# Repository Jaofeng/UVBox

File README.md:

# 自製 UV 紫外線曝光控制器
本控制器以 Arduino 的 ATMEGA328P 為核心，控制 UV LED 燈板，作為 DIY PCB 曝光用。

## 目錄
* [控制器硬體概要說明](#控制器硬體概要說明)
* [Arduino 程式功能](#arduino-程式功能)
* [原理圖與板線圖](#原理圖與板線圖)
* [實做範例](#實做範例)

## 控制器硬體概要說明
控制器分為兩版本：595 版與 I2C LCD 版。  
兩版本電路、功能都大同小異，最大差別在於 595 版是使用 74x595 控制七段顯示器作為顯示；I2C LCD 則是使用 PCF8574 控制 1602 的 LCD(相容HD44780)。  
I2C LCD 版提供 USB 界面(使用 FT232R)，可直接修改 Arduino 程式；而 595 版本就必須使用 ICSP 界面進行更新。

使用 4 + 1 個按鍵共 5 個按鍵進行控制：
* Start : 開始曝光
* Mode : 選擇模式  
    * 同時點亮上下兩板  
    * 僅點亮上板  
    * 僅點亮下板  
    * 亮度調整模式  
* Up / Dn :  
    * 亮度調整模式：增加/減少亮度值，增減量 +/- 5%
    * 其餘模式：增加/減少秒數，增減量 10 秒
* Reset : 重新啟動

595 版是第一個版本，小弟先用麵包版電路作第一片 595 版的 PCB，再用他去做其他的 PCB。

使用一般 Notebook 電源供應器(DC 19V)做為電源輸入，由於電路主要電壓使用 5V，為避免壓差太大，造成降壓晶片過熱燒毀，所以我做了兩次降壓：19v -> 12v -> 5v。  
由 ULN2003 控制 UV LED 燈板，也就是燈板部分直接使用 19V 電源。

在此不提供 UV LED 燈板的電路，我使用 5 串 1 並 14 的方式組成一片燈板，意思就是 5 顆 UV LED 與 1 顆限流電阻為一組做串聯，一共有 14 組併聯(請參閱下方照片)。    
LED 間距約為 7 x 2.54 mm。

依 LED 編排密度、曝光亮度、燈板高度、線路複雜度、感光 PCB 有效期、遮色片材質等等因素，都會互相影響，所以建議各位自行實驗，找出適合的亮度、時間與燈板高度。

以小弟的經驗是：
* 線路片使用噴墨投影片，兩張重疊，增加黑色遮光效果
* 燈板高度約 7cm
* 亮度 70%
* 時間 90s~110s 不等

以上述條件，即可成功製作一片漂亮的 PCB 線路。

對了，很基本的一件事：遮色片與感光 PCB 一定要夾緊，不能有任何間隙，否則非常容易失敗。

還有，UV 紫外線很傷眼睛，為了您的眼睛著想，建議戴著抗 UV 的鏡片，以及也不要讓皮膚長時間曝曬紫外線的環境下喔... 

***

## Arduino 程式功能
開始曝光後，會顯示倒數時間，曝光時間結束時會將燈板關閉且蜂鳴器會發出警示音。

控制功能：
* 可單一控制上下燈板
* 亮度調整範圍自 0% ~ 100%
* 時間可調整範圍自 0s ~ 600s
* 曝光時間結束時，自動關閉光板，並響起警示音
* 警示音響起時，按任何一鍵停止響音

***
## 原理圖與板線圖
595版  

I2C LCD版  

***
## 實做範例
UV LED 燈板與控制板(595)    

595 版正反面    

自製 USB to UART 轉接板

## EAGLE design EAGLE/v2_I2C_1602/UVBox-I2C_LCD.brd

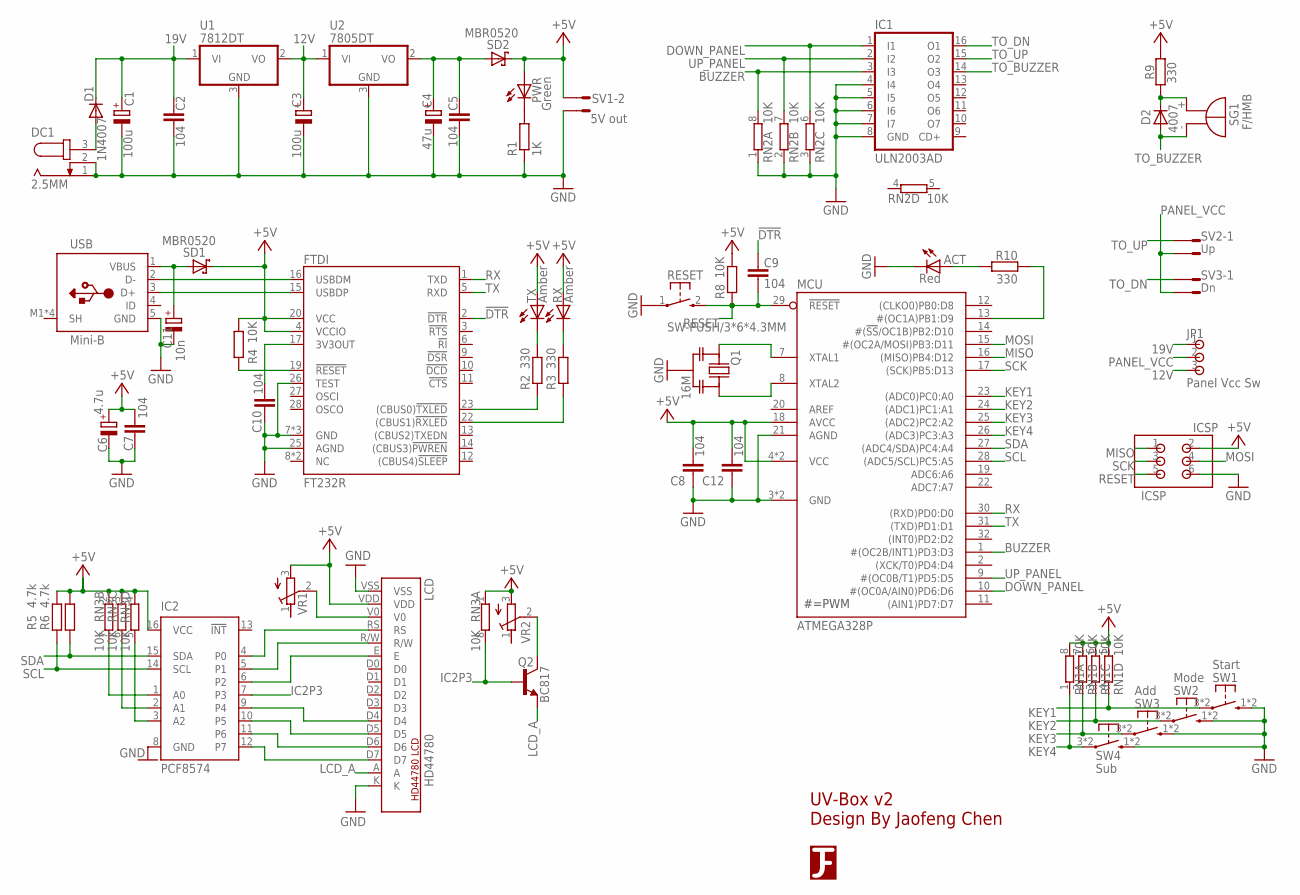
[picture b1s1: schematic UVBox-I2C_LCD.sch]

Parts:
ACT: Red; CHIPLED_0805
C1: 100u; 140CLH-0810
C2, C5: 104; C0805
C3: 100u; SMC_C
C4: 47u; SMC_C
C6: 4.7u; SMC_B
C7, C8, C9, C10, C12: 104; C0603
C11: 10n; SMC_A
D1: 1N4007; DO-214AC
D2: 4007; DO214AA
DC1: 2.5MM; SPC4078
FTDI: FT232R; SSOP28
IC1: ULN2003AD; SO16(R-PDSO-G16)
IC2: PCF8574; SO16W
ICSP: ICSP; DIP-2.54-2X3
JP1: Panel Vcc Sw; DIP-2.54-1X3
LCD: HD44780; LCD_1602
MCU: ATMEGA328P; TQFP32
PWR: Green; CHIPLED_0805
Q1: 16M; CSTCE
Q2: BC817; SOT23-BEC
R1: 1K; R0603
R2, R3, R9, R10: 330; R0603
R4, R8: 10K; R0603
R5, R6: 4.7k; R0603
RESET: SW-PUSH/3*6*4.3MM; SW-3*6*4.3MM
RN1, RN2, RN3: 10K; CAY16
RX: Amber; CHIPLED_0805
SD1, SD2: MBR0520; SOD123
SG1: F/HMB
SV1: 5V out; L02P
SV2: Up; L02P
SV3: Dn; L02P
SW1: Start; SW-6*6*3.8MM
SW2: Mode; SW-6*6*3.8MM
SW3: Add; SW-6*6*3.8MM
SW4: Sub; SW-6*6*3.8MM
TX: Amber; CHIPLED_0805
U1: 7812DT; TO252
U2: 7805DT; TO252
U$2: LOGO-3B; LOGO-3-B
USB: Mini-B; USB-MINI-B(NO_HOLE)
VR1, VR2: R-TRIMMT93XA; RTRIMT93XA

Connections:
12V: C3.+, JP1.3, U1.2 (VO), U2.1 (VI)
19V: C1.+, C2.1, D1.C, JP1.1, U1.1 (VI)
!DTR: C9.2, FTDI.2 (!DTR)
!RESET: FTDI.19 (!RESET), R4.1
!RXLED: FTDI.22 ((CBUS1)!RXLED), R3.1
!TXLED: FTDI.23 ((CBUS0)!TXLED), R2.1
+5V: C6.+, C7.1, C8.2, C12.2, FTDI.4 (VCCIO), FTDI.20 (VCC), IC2.16 (VCC), ICSP.2, LCD.VDD, MCU.4 (VCC), MCU.6 (VCC), MCU.18 (AVCC), PWR.A, R4.2, R5.1, R6.1, R8.2, R9.2, RN1.5 (2), RN1.6 (2), RN1.7 (2), RN1.8 (2), RN3.1, RN3.2 (1), RN3.3 (1), RN3.4 (1), RX.A, SD1.K, SD2.K, SV1.2, TX.A, VR1.3 (A), VR2.3 (A)
A0: IC2.1 (A0), RN3.7 (2)
A1: IC2.2 (A1), RN3.6 (2)
A2: IC2.3 (A2), RN3.5 (2)
ACT_LED: ACT.A, R10.2
BUZZER: IC1.3 (I3), MCU.1 (#(OC2B/INT1)PD3:D3), RN2.8 (2)
D+: FTDI.15 (USBDP), USB.3 (D+)
D-: FTDI.16 (USBDM), USB.2 (D-)
DOWN_PANEL: IC1.1 (I1), MCU.10 (#(OC0A/AIN0)PD6:D6), RN2.6 (2)
E: IC2.6 (P2), LCD.E
GND: ACT.C, C1.-, C2.2, C3.-, C4.-, C5.2, C6.-, C7.2, C8.1, C10.1, C11.-, C12.1, DC1.1, DC1.2, FTDI.7 (GND), FTDI.18 (GND), FTDI.21 (GND), FTDI.25 (AGND), FTDI.26 (TEST), IC1.4 (I4), IC1.5 (I5), IC1.6 (I6), IC1.7 (I7), IC1.8 (GND), IC2.8 (GND), ICSP.6, LCD.K, LCD.VSS, MCU.3 (GND), MCU.5 (GND), MCU.21 (AGND), Q1.2 (GND), R1.1, RESET.1, RN2.1, RN2.2 (1), RN2.3 (1), SV1.1, SW1.1 (S), SW1.2 (S), SW2.1 (S), SW2.2 (S), SW3.1 (S), SW3.2 (S), SW4.1 (S), SW4.2 (S), U1.3 (GND), U2.3 (GND), USB.5 (GND)
IC2P3: IC2.7 (P3), Q2.B, RN3.8 (2)
KEY1: MCU.23 ((ADC0)PC0:A0), RN1.4 (1), SW1.3, SW1.4
KEY2: MCU.24 ((ADC1)PC1:A1), RN1.3 (1), SW2.3, SW2.4
KEY3: MCU.25 ((ADC2)PC2:A2), RN1.2 (1), SW3.3, SW3.4
KEY4: MCU.26 ((ADC3)PC3:A3), RN1.1, SW4.3, SW4.4
LCD_A: LCD.A, Q2.E
MISO: ICSP.1, MCU.16 ((MISO)PB4:D12)
MOSI: ICSP.4, MCU.15 (#(OC2A/MOSI)PB3:D11)
unnamed: C11.+, SD1.A, USB.1 (VBUS)
unnamed: C4.+, C5.1, SD2.A, U2.2 (VO)
unnamed: D1.A, DC1.3
unnamed: PWR.C, R1.2
unnamed: Q2.C, VR2.2 (S)
unnamed: R2.2, TX.C
unnamed: R3.2, RX.C
unnamed: D2.C, R9.1, SG1.+
unnamed: IC2.12 (P7), LCD.D7
unnamed: IC2.11 (P6), LCD.D6
unnamed: IC2.10 (P5), LCD.D5
unnamed: IC2.9 (P4), LCD.D4
unnamed: C10.2, FTDI.17 (3V3OUT)
PANEL_VCC: JP1.2, SV2.2, SV3.2
PB1: MCU.13 (#(OC1A)PB1:D9), R10.1
R/W: IC2.5 (P1), LCD.R/W
RESET: C9.1, ICSP.5, MCU.29 (!RESET), R8.1, RESET.2 (S)
RS: IC2.4 (P0), LCD.RS
RX: FTDI.1 (TXD), MCU.30 ((RXD)PD0:D0)
SCK: ICSP.3, MCU.17 ((SCK)PB5:D13)
SCL: IC2.14 (SCL), MCU.28 ((ADC5/SCL)PC5:A5), R5.2
SDA: IC2.15 (SDA), MCU.27 ((ADC4/SDA)PC4:A4), R6.2
TO_BUZZER: D2.A, IC1.14 (O3), SG1.-
TO_DN: IC1.16 (O1), SV3.1
TO_UP: IC1.15 (O2), SV2.1
TX: FTDI.5 (RXD), MCU.31 ((TXD)PD1:D1)
UP_PANEL: IC1.2 (I2), MCU.9 (#(OC0B/T1)PD5:D5), RN2.7 (2)
VD: LCD.V0, VR1.2 (S)
XTAL1: MCU.7 (XTAL1), Q1.1 (IN)
XTAL2: MCU.8 (XTAL2), Q1.3 (OUT)

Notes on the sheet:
UV-Box v2 Design By Jaofeng Chen

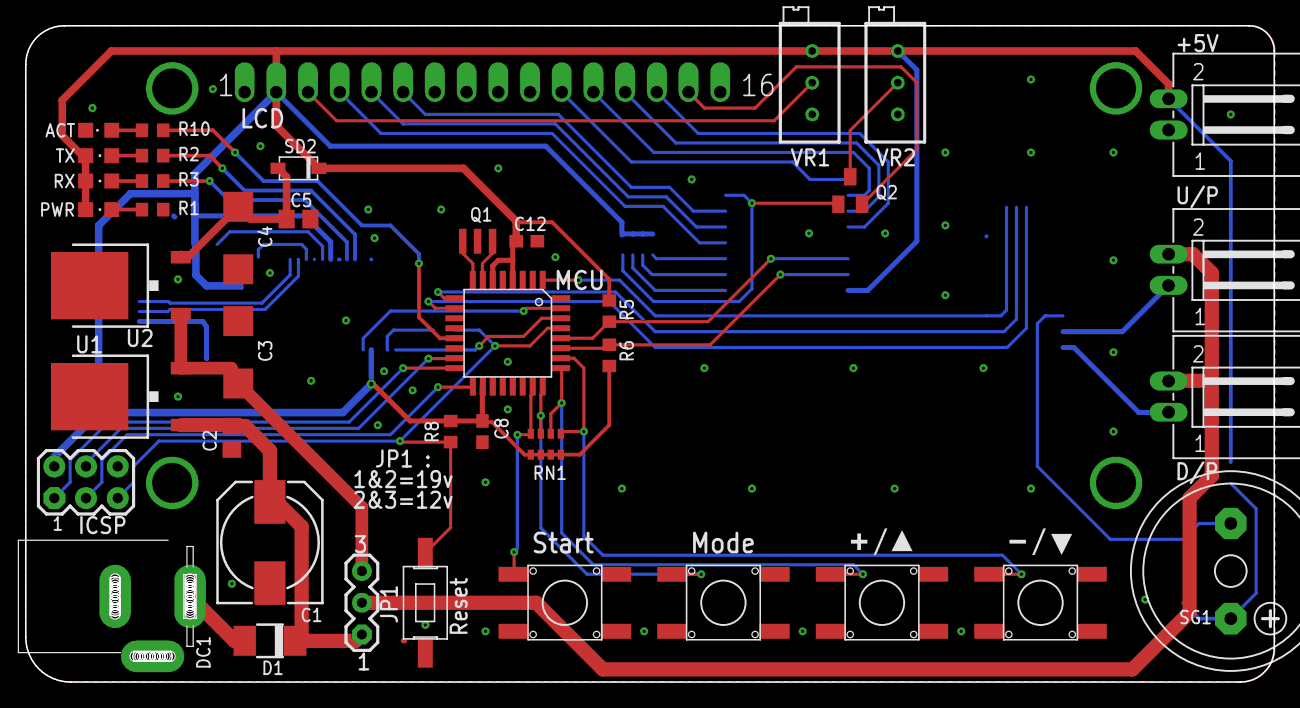
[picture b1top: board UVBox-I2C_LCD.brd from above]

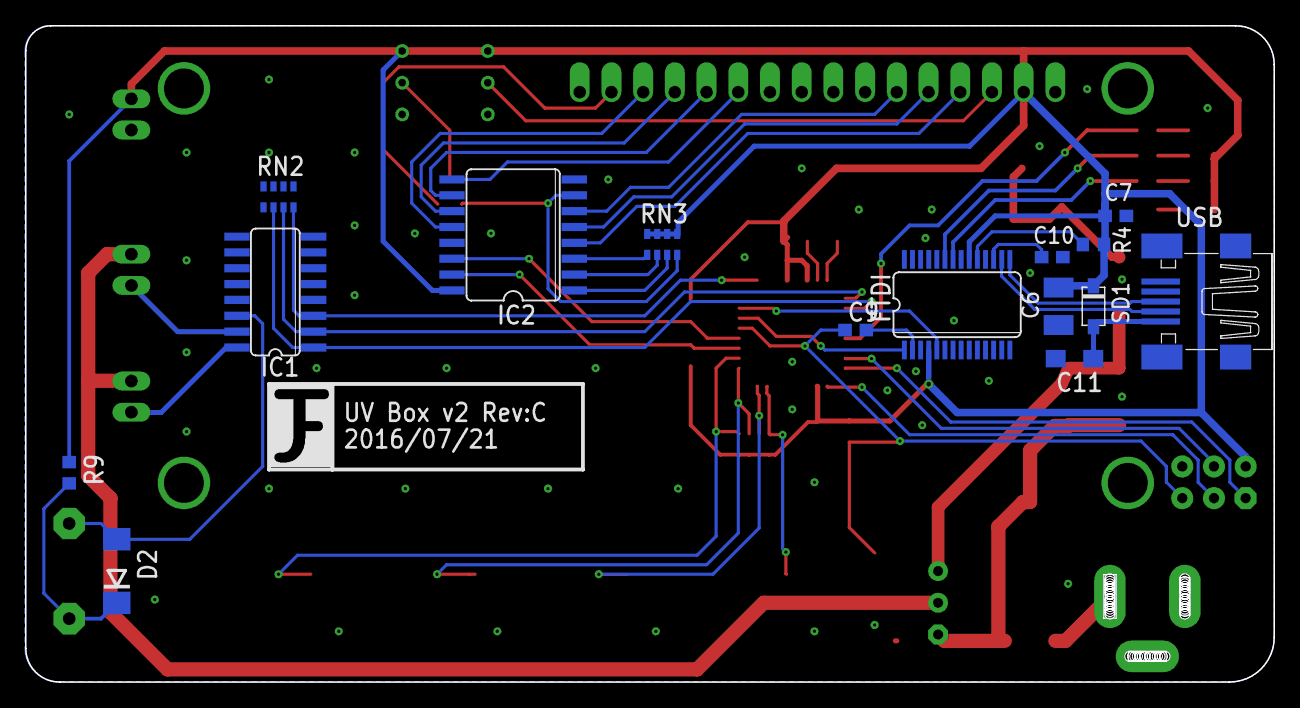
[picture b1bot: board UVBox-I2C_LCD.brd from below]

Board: 2 copper layers, 100.0 x 52.6 mm, 59 parts (15 on the bottom side), 55 nets.

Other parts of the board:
U$1: TEXT_UP
U$3: TEXT_DN

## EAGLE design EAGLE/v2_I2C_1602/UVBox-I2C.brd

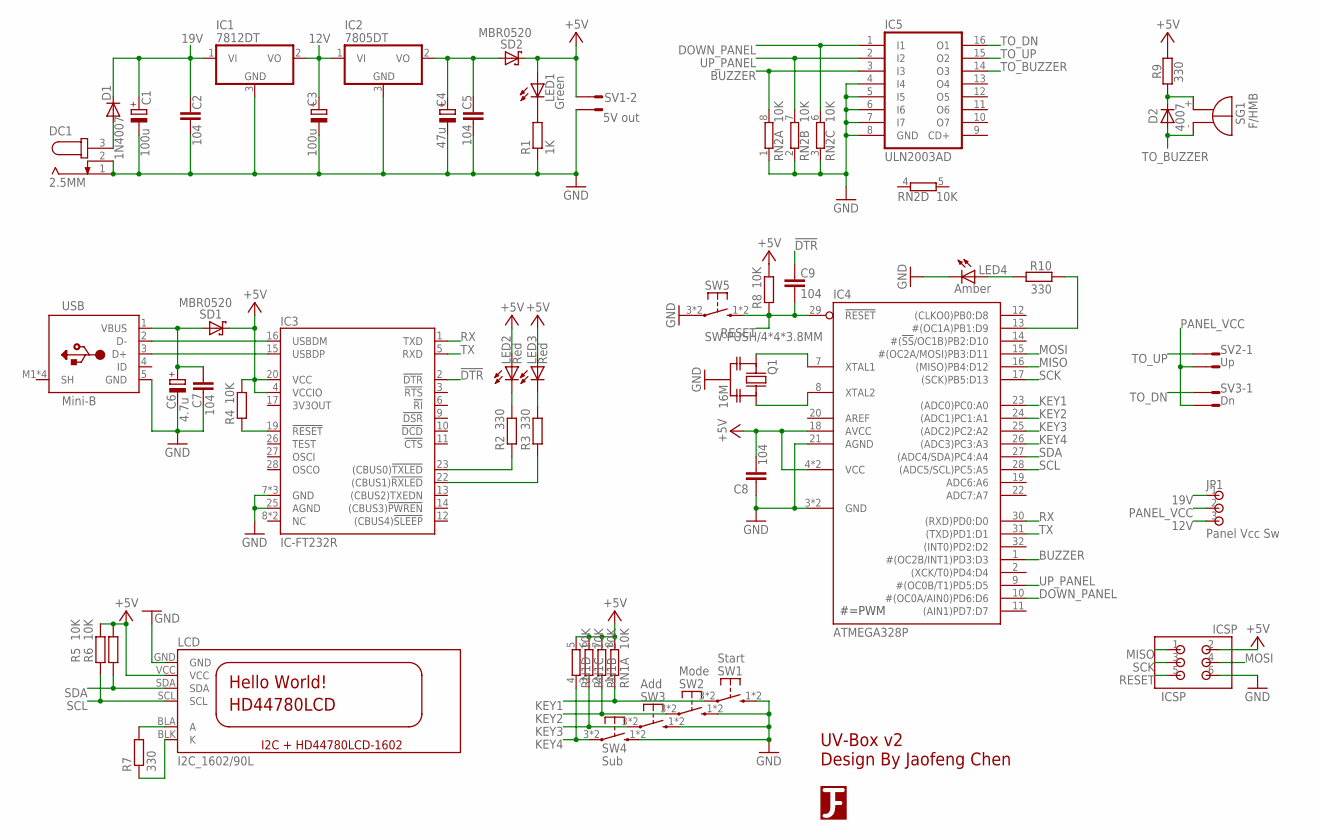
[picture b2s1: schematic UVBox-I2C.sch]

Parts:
C1: 100u; 140CLH-0810
C2, C5, C7, C8, C9: 104; C0805
C3: 100u; SMC_C
C4: 47u; SMC_C
C6: 4.7u; SMC_C
D1: 1N4007; DO-214AC
D2: 4007; DO214AA
DC1: 2.5MM; SPC4078
IC1: 7812DT; TO252
IC2: 7805DT; TO252
IC3: IC-FT232R; SSOP28
IC4: ATMEGA328P; TQFP32
IC5: ULN2003AD; SO16
ICSP: ICSP; DIP-2.54-2X3
JP1: Panel Vcc Sw; DIP-2.0-1X3
LCD: I2C_1602/90L
LED1: Green; CHIPLED_1206
LED2, LED3: Red; CHIPLED_1206
LED4: Amber; CHIPLED_1206
Q1: 16M; CSTCE
R1: 1K; R0805
R2, R3, R7, R9, R10: 330; R0805
R4, R5, R6, R8: 10K; R0805
RN1, RN2: 10K; CAY16
SD1, SD2: MBR0520; SOD123
SG1: F/HMB
SV1: 5V out; L02P
SV2: Up; L02P
SV3: Dn; L02P
SW1: Start; SW-6*6*3.8MM
SW2: Mode; SW-6*6*3.8MM
SW3: Add; SW-6*6*3.8MM
SW4: Sub; SW-6*6*3.8MM
SW5: SW-PUSH/4*4*3.8MM; SW-4*4*3.8MM
U$2: LOGO-3
USB: Mini-B; USB-MINI-B(NO_HOLE)

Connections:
12V: C3.+, IC1.2 (VO), IC2.1 (VI), JP1.3
19V: C1.+, C2.1, D1.C, IC1.1 (VI), JP1.1
!DTR: C9.2, IC3.2 (!DTR)
+5V: C8.2, IC3.4 (VCCIO), IC3.20 (VCC), IC4.4 (VCC), IC4.6 (VCC), IC4.18 (AVCC), ICSP.2, LCD.VCC, LED1.A, LED2.A, LED3.A, R4.2, R5.1, R6.1, R8.2, R9.2, RN1.5 (2), RN1.6 (2), RN1.7 (2), RN1.8 (2), SD1.K, SD2.K, SV1.2
BUZZER: IC4.1 (#(OC2B/INT1)PD3:D3), IC5.3 (I3), RN2.8 (2)
DOWN_PANEL: IC4.10 (#(OC0A/AIN0)PD6:D6), IC5.1 (I1), RN2.6 (2)
GND: C1.-, C2.2, C3.-, C4.-, C5.2, C6.-, C7.2, C8.1, DC1.1, DC1.2, IC1.3 (GND), IC2.3 (GND), IC3.7 (GND), IC3.18 (GND), IC3.21 (GND), IC3.25 (AGND), IC4.3 (GND), IC4.5 (GND), IC4.21 (AGND), IC5.4 (I4), IC5.5 (I5), IC5.6 (I6), IC5.7 (I7), IC5.8 (GND), ICSP.6, LCD.GND, LED4.C, Q1.2 (GND), R1.1, RN2.1, RN2.2 (1), RN2.3 (1), SV1.1, SW1.1 (S), SW1.2 (S), SW2.1 (S), SW2.2 (S), SW3.1 (S), SW3.2 (S), SW4.1 (S), SW4.2 (S), SW5.3, SW5.4, USB.5 (GND)
KEY1: IC4.23 ((ADC0)PC0:A0), RN1.1, SW1.3, SW1.4
KEY2: IC4.24 ((ADC1)PC1:A1), RN1.2 (1), SW2.3, SW2.4
KEY3: IC4.25 ((ADC2)PC2:A2), RN1.3 (1), SW3.3, SW3.4
KEY4: IC4.26 ((ADC3)PC3:A3), RN1.4 (1), SW4.3, SW4.4
MISO: IC4.16 ((MISO)PB4:D12), ICSP.1
MOSI: IC4.15 (#(OC2A/MOSI)PB3:D11), ICSP.4
unnamed: C6.+, C7.1, SD1.A, USB.1 (VBUS)
unnamed: C4.+, C5.1, IC2.2 (VO), SD2.A
unnamed: D1.A, DC1.3
unnamed: IC3.19 (!RESET), R4.1
unnamed: IC4.7 (XTAL1), Q1.1 (IN)
unnamed: LED1.C, R1.2
unnamed: IC3.16 (USBDM), USB.2 (D-)
unnamed: LCD.BLK (K), R7.1
unnamed: LCD.BLA (A), R7.2
unnamed: IC3.15 (USBDP), USB.3 (D+)
unnamed: LED2.C, R2.2
unnamed: LED3.C, R3.2
unnamed: D2.C, R9.1, SG1.+
unnamed: IC3.23 ((CBUS0)!TXLED), R2.1
unnamed: IC3.22 ((CBUS1)!RXLED), R3.1
unnamed: LED4.A, R10.2
unnamed: IC4.13 (#(OC1A)PB1:D9), R10.1
unnamed: IC4.8 (XTAL2), Q1.3 (OUT)
PANEL_VCC: JP1.2, SV2.2, SV3.2
RESET: C9.1, IC4.29 (!RESET), ICSP.5, R8.1, SW5.1 (S), SW5.2 (S)
RX: IC3.1 (TXD), IC4.30 ((RXD)PD0:D0)
SCK: IC4.17 ((SCK)PB5:D13), ICSP.3
SCL: IC4.28 ((ADC5/SCL)PC5:A5), LCD.SCL, R5.2
SDA: IC4.27 ((ADC4/SDA)PC4:A4), LCD.SDA, R6.2
TO_BUZZER: D2.A, IC5.14 (O3), SG1.-
TO_DN: IC5.16 (O1), SV3.1
TO_UP: IC5.15 (O2), SV2.1
TX: IC3.5 (RXD), IC4.31 ((TXD)PD1:D1)
UP_PANEL: IC4.9 (#(OC0B/T1)PD5:D5), IC5.2 (I2), RN2.7 (2)

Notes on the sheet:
UV-Box v2 Design By Jaofeng Chen

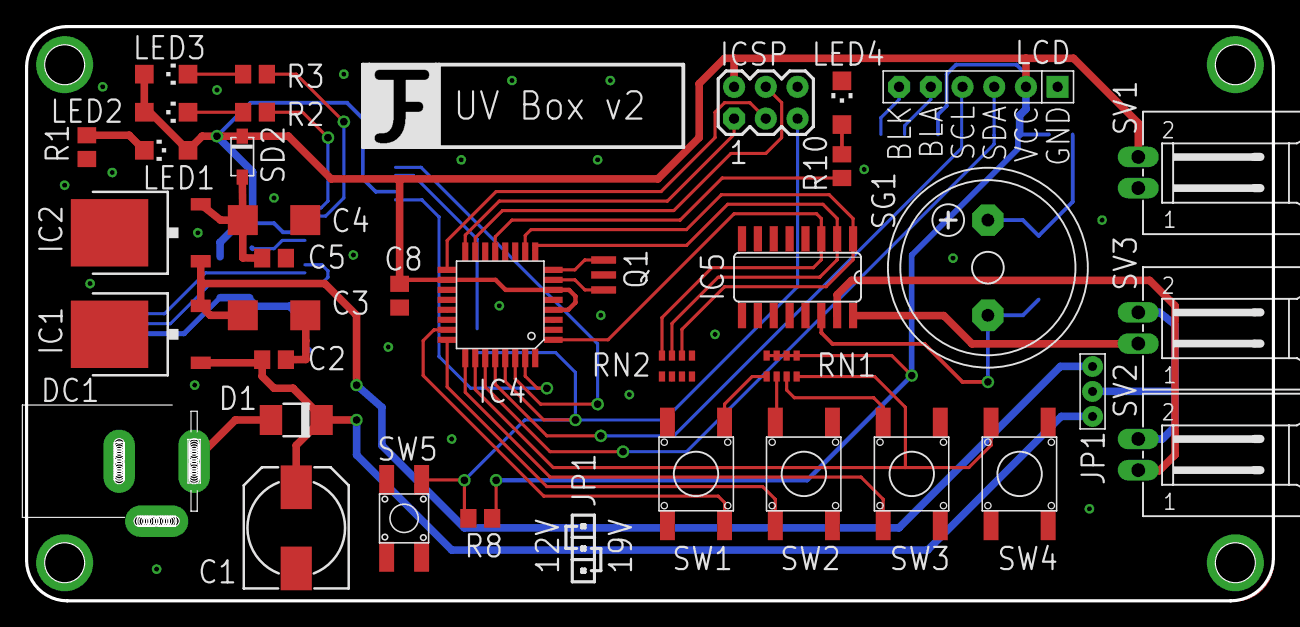
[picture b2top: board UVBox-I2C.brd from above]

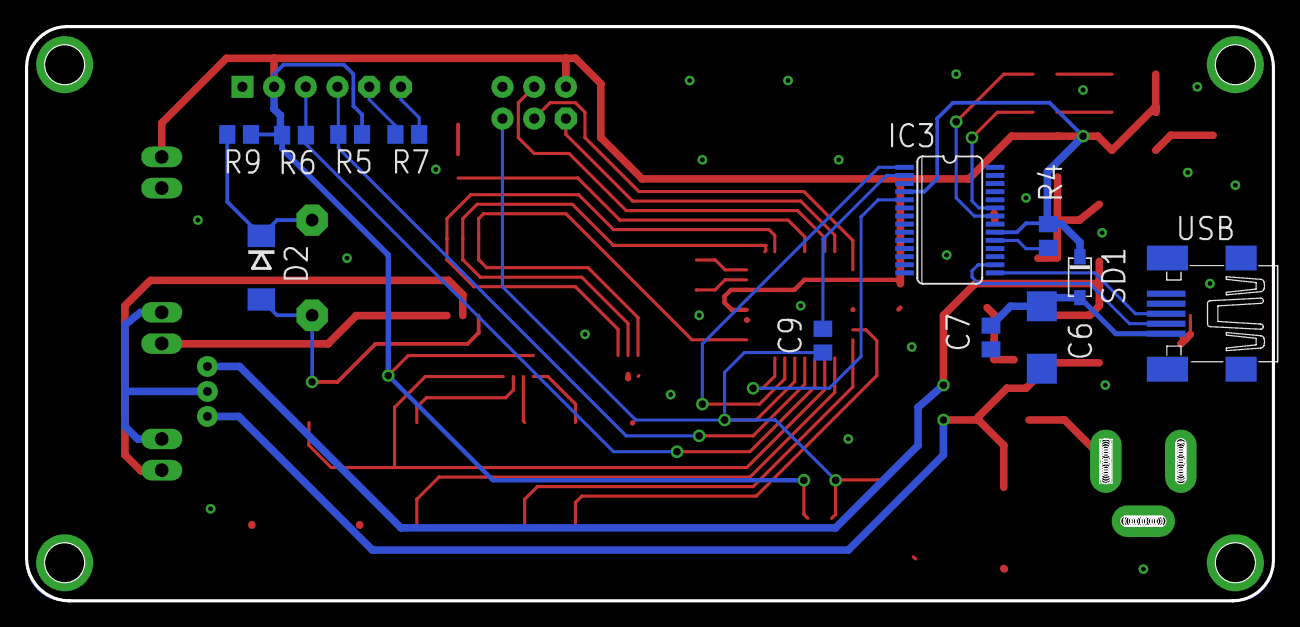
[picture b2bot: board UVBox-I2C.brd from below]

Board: 2 copper layers, 99.8 x 46.0 mm, 50 parts (12 on the bottom side), 42 nets.

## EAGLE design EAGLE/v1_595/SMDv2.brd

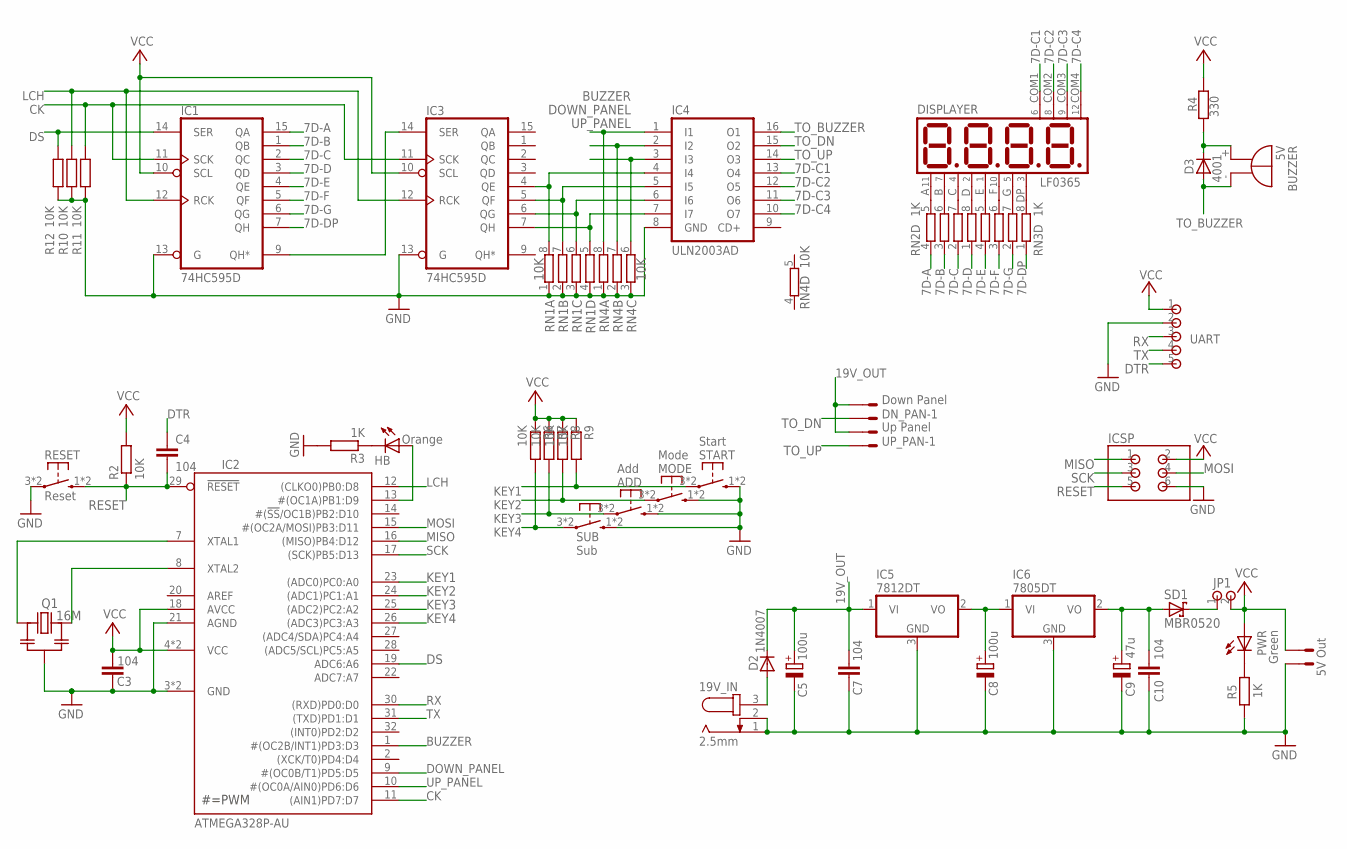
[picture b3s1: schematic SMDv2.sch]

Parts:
5V_OUT: 5V Out; L02P
19V_IN: 2.5mm; SPC4078
ADD: Add; SW-6*6*3.8MM
BUZZER: 5V; BZ-5V
C3, C4, C7, C10: 104; C0805
C5: 100u; 140CLH-0810
C8: 100u; SMC_C
C9: 47u; SMC_C
D2: 1N4007; DO-214AC
D3: 4001; DO-214AC
DISPLAYER: LF0365; LF036*
DN_PAN: Down Panel; L02P
HB: Orange; CHIPLED_1206
IC1, IC3: 74HC595D; SO16
IC2: ATMEGA328P-AU; TQFP32
IC4: ULN2003AD; SO16
IC5: 7812DT; TO252
IC6: 7805DT; TO252
ICSP: PIN-2X3/DIP; DIP-2.54-2X3
JP1: PIN-1X2-2.54; DIP-2.54-1X2
MODE: Mode; SW-6*6*3.8MM
PWR: Green; CHIPLED_1206
Q1: 16M; CSTCE
R2, R6, R7, R8, R9, R10, R11, R12: 10K; R0805
R3, R5: 1K; R0805
R4: 330; R0805
RESET: Reset; SW-4*4*3.8MM
RN1, RN4: 10K; CAY16
RN2, RN3: 1K; CAY16
SD1: MBR0520; SOD123
START: Start; SW-6*6*3.8MM
SUB: Sub; SW-6*6*3.8MM
UART: PIN-1X5-2.54; DIP-2.54-1X5
UP_PAN: Up Panel; L02P

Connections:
7D-A: IC1.15 (QA), RN2.4 (1)
7D-B: IC1.1 (QB), RN2.3 (1)
7D-C: IC1.2 (QC), RN2.2 (1)
7D-C1: DISPLAYER.COM1, IC4.13 (O4)
7D-C2: DISPLAYER.COM2, IC4.12 (O5)
7D-C3: DISPLAYER.COM3, IC4.11 (O6)
7D-C4: DISPLAYER.COM4, IC4.10 (O7)
7D-D: IC1.3 (QD), RN2.1
7D-DP: IC1.7 (QH), RN3.1
7D-E: IC1.4 (QE), RN3.4 (1)
7D-F: IC1.5 (QF), RN3.3 (1)
7D-G: IC1.6 (QG), RN3.2 (1)
12V: C8.+, IC5.2 (VO), IC6.1 (VI)
19V_OUT: C5.+, C7.1, D2.C, DN_PAN.2, IC5.1 (VI), UP_PAN.2
BUZZER: IC2.1 (#(OC2B/INT1)PD3:D3), IC4.1 (I1), RN4.8 (2)
CK: IC1.11 (SCK), IC2.11 ((AIN1)PD7:D7), IC3.11 (SCK), R11.2
DOWN_PANEL: IC2.9 (#(OC0B/T1)PD5:D5), IC4.2 (I2), RN4.7 (2)
DS: IC1.14 (SER), IC2.19 (ADC6:A6), R12.2
DTR: C4.1, UART.5
GND: 5V_OUT.1, 19V_IN.1, 19V_IN.2, ADD.1 (S), ADD.2 (S), C3.1, C5.-, C7.2, C8.-, C9.-, C10.2, IC1.8 (GND), IC1.13 (G), IC2.3 (GND), IC2.5 (GND), IC2.21 (AGND), IC3.8 (GND), IC3.13 (G), IC4.8 (GND), IC5.3 (GND), IC6.3 (GND), ICSP.6, MODE.1 (S), MODE.2 (S), Q1.2 (GND), R3.2, R5.1, R10.1, R11.1, R12.1, RESET.3, RESET.4, RN1.1, RN1.2 (1), RN1.3 (1), RN1.4 (1), RN4.1, RN4.2 (1), RN4.3 (1), START.1 (S), START.2 (S), SUB.1 (S), SUB.2 (S), UART.2
KEY1: IC2.23 ((ADC0)PC0:A0), R9.2, START.3, START.4
KEY2: IC2.24 ((ADC1)PC1:A1), MODE.3, MODE.4, R8.2
KEY3: ADD.3, ADD.4, IC2.25 ((ADC2)PC2:A2), R7.2
KEY4: IC2.26 ((ADC3)PC3:A3), R6.2, SUB.3, SUB.4
LCH: IC1.12 (RCK), IC2.12 ((CLKO0)PB0:D8), IC3.12 (RCK), R10.2
MISO: IC2.16 ((MISO)PB4:D12), ICSP.1
MOSI: IC2.15 (#(OC2A/MOSI)PB3:D11), ICSP.4
unnamed: 19V_IN.3, D2.A
unnamed: C9.+, C10.1, IC6.2 (VO), SD1.A
unnamed: JP1.1, SD1.K
unnamed: HB.C, R3.1
unnamed: DISPLAYER.A, RN2.5 (2)
unnamed: IC3.4 (QE), IC4.4 (I4), RN1.8 (2)
unnamed: IC2.7 (XTAL1), Q1.1 (IN)
unnamed: PWR.C, R5.2
unnamed: IC1.9 (QH*), IC3.14 (SER)
unnamed: IC3.5 (QF), IC4.5 (I5), RN1.7 (2)
unnamed: DISPLAYER.B, RN2.6 (2)
unnamed: IC3.6 (QG), IC4.6 (I6), RN1.6 (2)
unnamed: IC3.7 (QH), IC4.7 (I7), RN1.5 (2)
unnamed: BUZZER.+, D3.C, R4.1
unnamed: DISPLAYER.C, RN2.7 (2)
unnamed: DISPLAYER.D, RN2.8 (2)
unnamed: DISPLAYER.E, RN3.5 (2)
unnamed: DISPLAYER.F, RN3.6 (2)
unnamed: DISPLAYER.G, RN3.7 (2)
unnamed: DISPLAYER.DP, RN3.8 (2)
unnamed: HB.A, IC2.13 (#(OC1A)PB1:D9)
unnamed: IC2.8 (XTAL2), Q1.3 (OUT)
RESET: C4.2, IC2.29 (!RESET), ICSP.5, R2.1, RESET.1 (S), RESET.2 (S)
RX: IC2.30 ((RXD)PD0:D0), UART.3
SCK: IC2.17 ((SCK)PB5:D13), ICSP.3
TO_BUZZER: BUZZER.-, D3.A, IC4.16 (O1)
TO_DN: DN_PAN.1, IC4.15 (O2)
TO_UP: IC4.14 (O3), UP_PAN.1
TX: IC2.31 ((TXD)PD1:D1), UART.4
UP_PANEL: IC2.10 (#(OC0A/AIN0)PD6:D6), IC4.3 (I3), RN4.6 (2)
VCC: 5V_OUT.2, C3.2, IC1.10 (SCL), IC1.16 (VCC), IC2.4 (VCC), IC2.6 (VCC), IC2.18 (AVCC), IC3.10 (SCL), IC3.16 (VCC), ICSP.2, JP1.2, PWR.A, R2.2, R4.2, R6.1, R7.1, R8.1, R9.1, UART.1

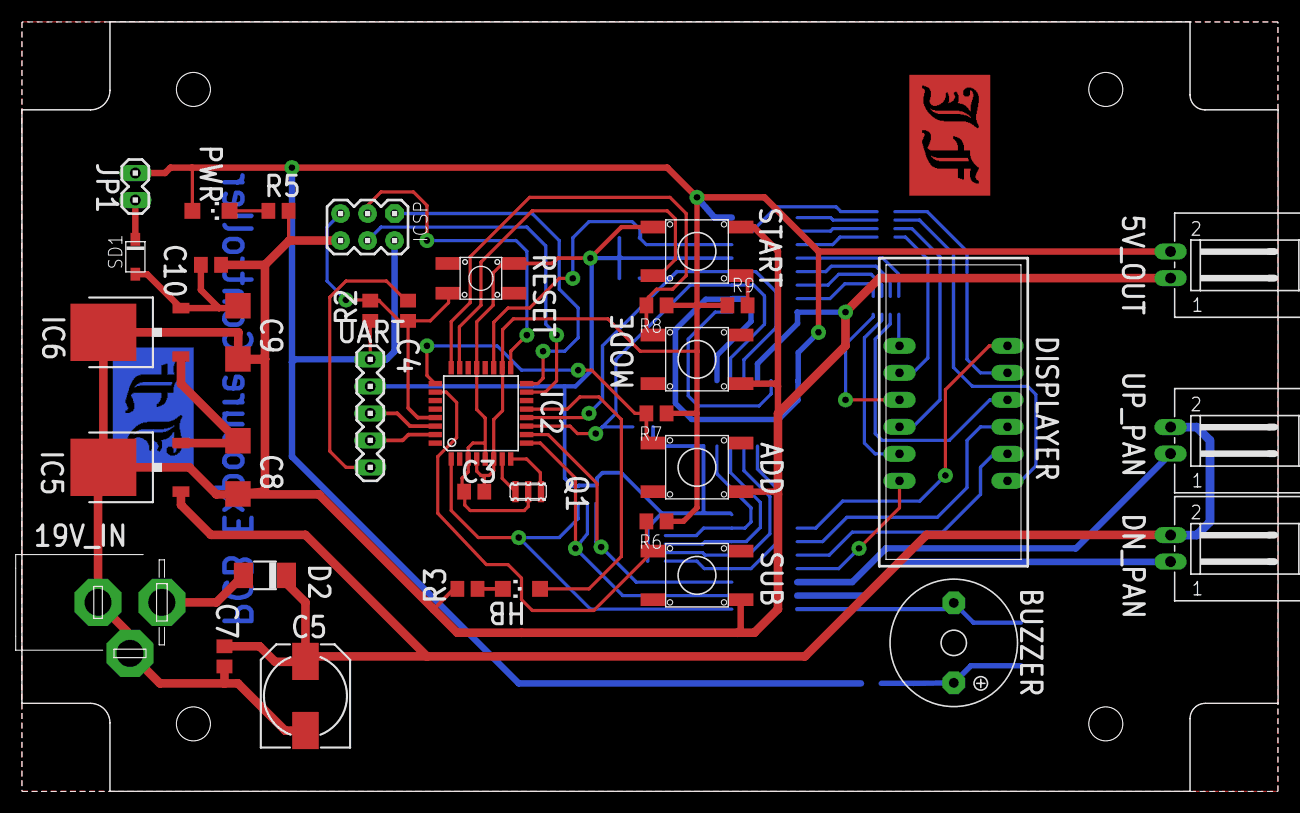
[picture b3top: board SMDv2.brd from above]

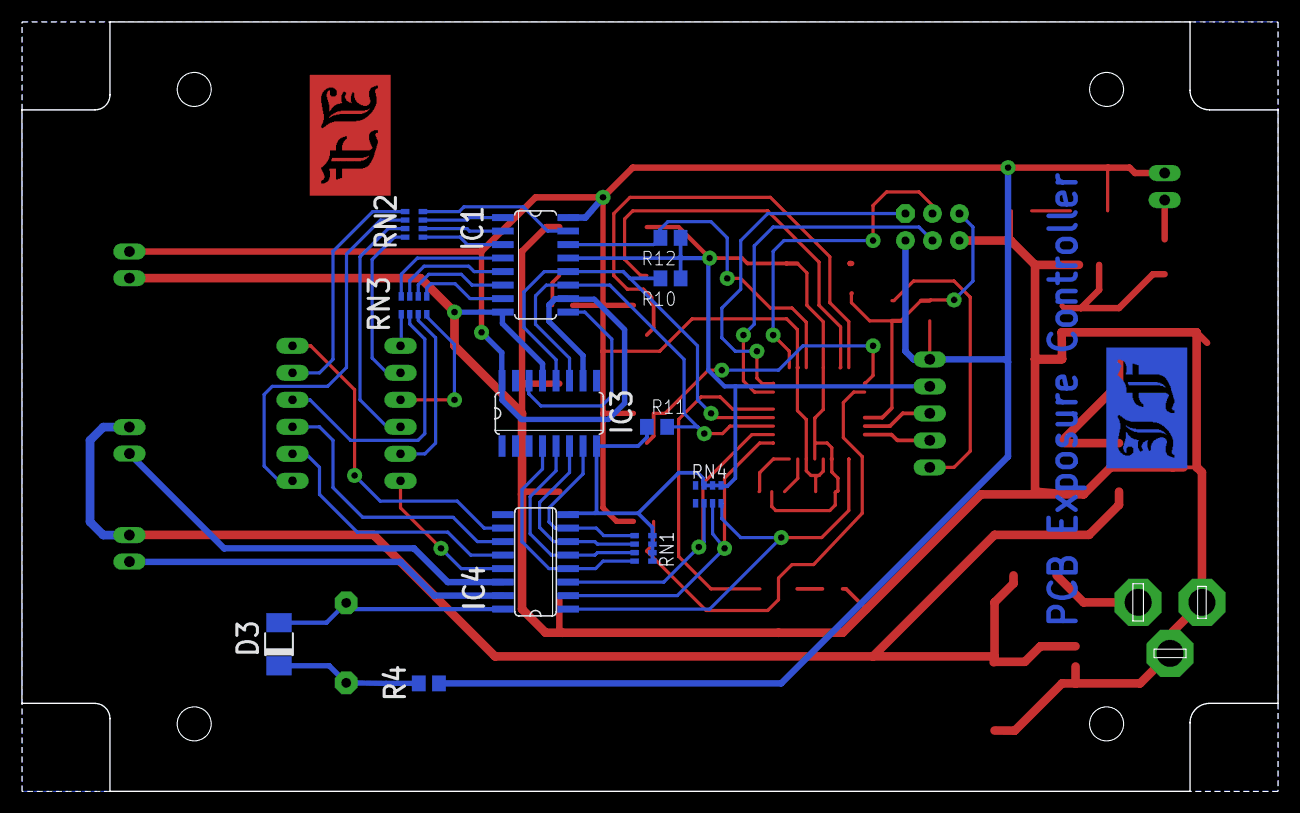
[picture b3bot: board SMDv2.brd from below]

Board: 2 copper layers, 118.2 x 72.4 mm, 49 parts (12 on the bottom side), 58 nets.

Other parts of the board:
U$1: CASE-1

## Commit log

2016-05-18 Rename folder
2016-05-18 完成 v1.00
2016-05-20 無關緊要的小修改
2016-05-20 小調整啟動時LCD的流程
2016-07-21 新增直接使用 LCD 結合母版的方式
2016-08-02 細微修改
2016-12-08 Ignore some files
2017-12-28 增加本說明文件
2017-12-29 Append Demo
2018-01-15 Append Images
2018-01-15 刪除舊Gerber
2018-01-15 Append Demo Images
2018-01-16 調整線路配置
2018-01-16 調整絲印字型大小
2018-01-25 更換零件與微調線路
